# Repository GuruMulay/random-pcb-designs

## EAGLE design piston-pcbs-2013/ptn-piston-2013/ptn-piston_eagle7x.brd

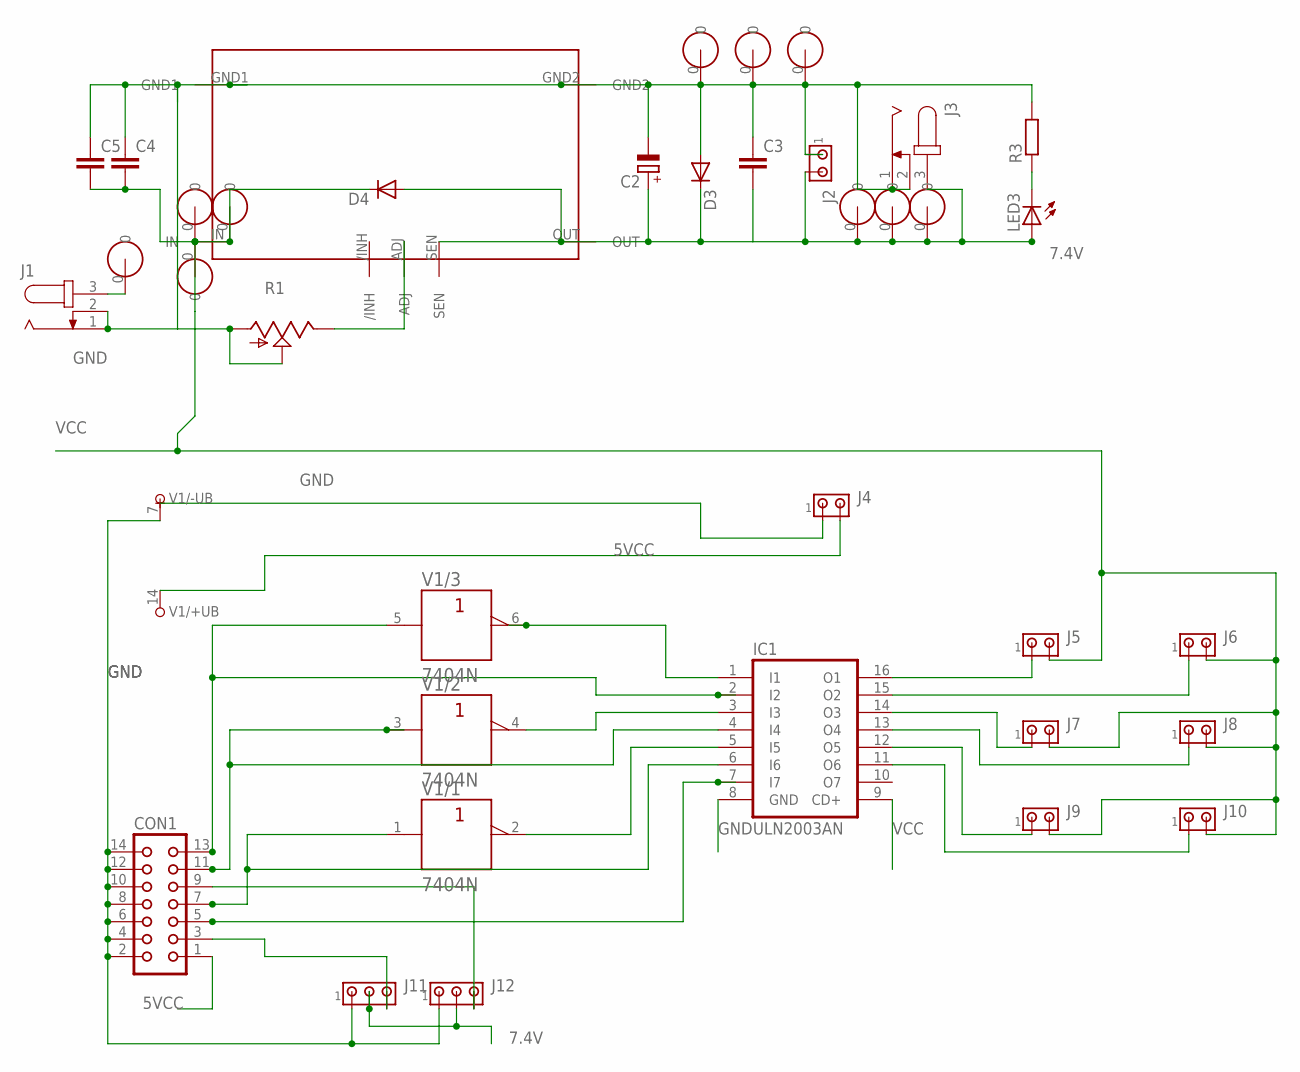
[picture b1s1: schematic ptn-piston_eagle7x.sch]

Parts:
C2: CPOL-EUE3.5-8; E3,5-8
C3, C4, C5: C-EUC1206K; C1206K
CON1: CON14
D3, D4: DIODE-SMB; SMB
IC1: ULN2003AN; DIL16
J1, J3: JACK-PLUG1; SPC4078
J2, J4, J5, J6, J7, J8, J9, J10: MTA02-100; 10X02MTA
J11, J12: MTA03-100; 10X03MTA
LED3: LED3MM
R1: TRIM_US-B64Y; B64Y
R3: R-EU_R0603; R0603
U$1: PTNPTN2; PTN
U$2: PAD0; SWITCHPAD
U$3, U$4, U$5, U$6, U$7, U$8, U$9, U$10, U$11: PADSWITCHPAD1; SWITCHPAD
V1: 7404N; DIL14

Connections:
5VCC: CON1.1, J4.2, V1.14 (+UB)
7.4V: C2.+, C3.2, D3.C, D4.A, J2.2, J3.3, J11.2, J12.2, LED3.A, U$1.OUT, U$1.SEN, U$5.0, U$7.0, U$9.0
GND: C2.-, C3.1, C4.1, C5.1, CON1.2, CON1.4, CON1.6, CON1.8, CON1.10, CON1.12, CON1.14, D3.A, IC1.8 (GND), J1.1, J1.2, J2.1, J3.1, J3.2, J4.1, J11.1, J12.1, R1.A, R1.S, R3.2, U$1.GND1, U$1.GND2, U$4.0, U$6.0, U$8.0, V1.7 (-UB)
unnamed: CON1.13, IC1.2 (I2), V1.5 (A)
unnamed: LED3.K (C), R3.1
unnamed: R1.E, U$1.ADJ
unnamed: CON1.11, IC1.4 (I4), V1.3 (A)
unnamed: J1.3, U$3.0
unnamed: CON1.7, IC1.6 (I6), V1.1 (A)
unnamed: IC1.5 (I5), V1.2 (Y)
unnamed: CON1.5, IC1.7 (I7)
unnamed: IC1.1 (I1), V1.6 (Y)
unnamed: IC1.3 (I3), V1.4 (Y)
unnamed: CON1.3, J11.3
unnamed: CON1.9, J12.3
unnamed: IC1.16 (O1), J5.1
unnamed: IC1.15 (O2), J6.1
unnamed: IC1.14 (O3), J7.1
unnamed: IC1.13 (O4), J8.1
unnamed: IC1.12 (O5), J9.1
unnamed: IC1.11 (O6), J10.1
VCC: C4.2, C5.2, D4.C, IC1.9 (CD+), J5.2, J6.2, J7.2, J8.2, J9.2, J10.2, U$1.IN, U$2.0, U$10.0, U$11.0

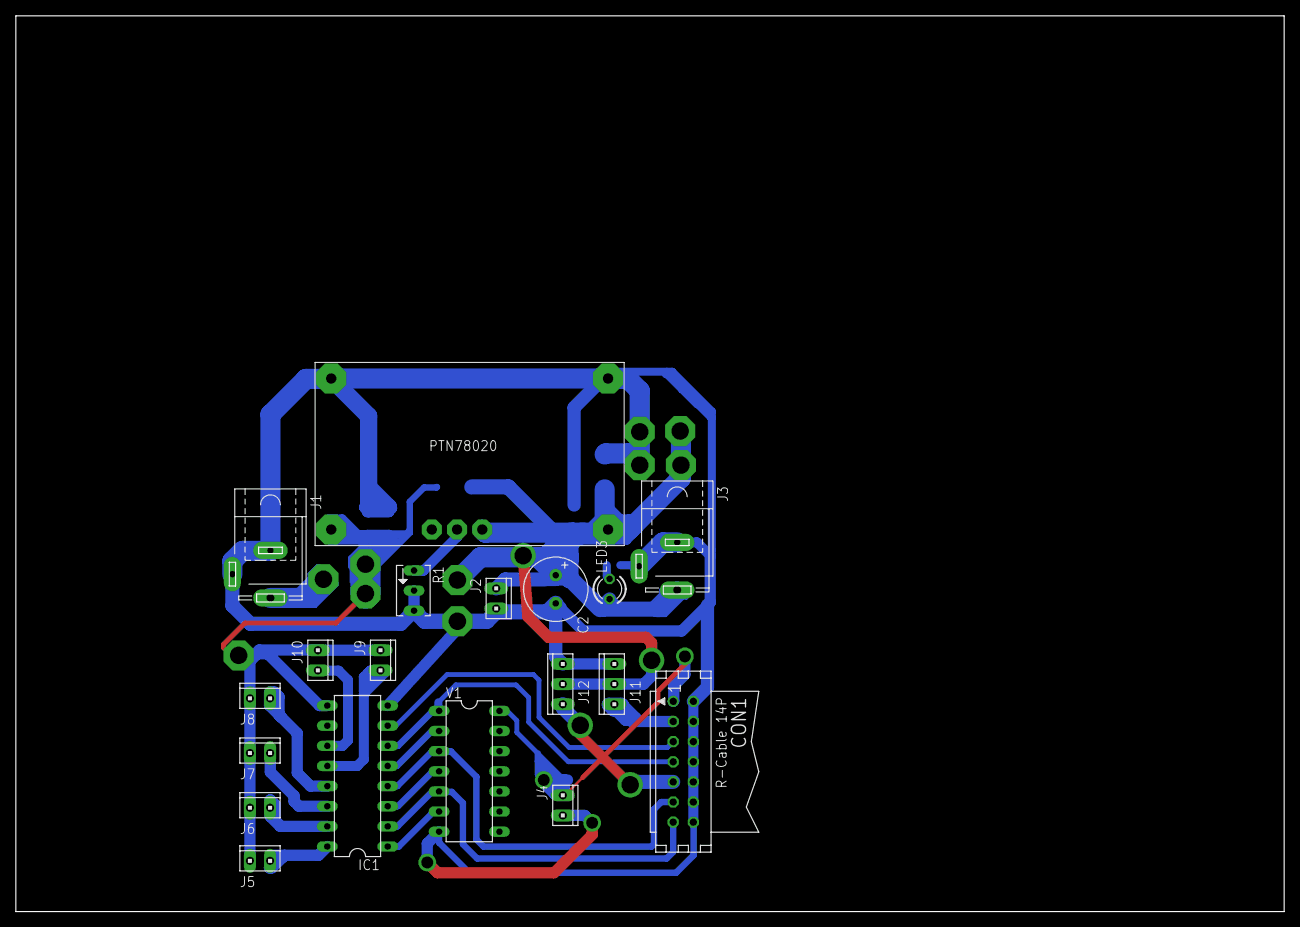
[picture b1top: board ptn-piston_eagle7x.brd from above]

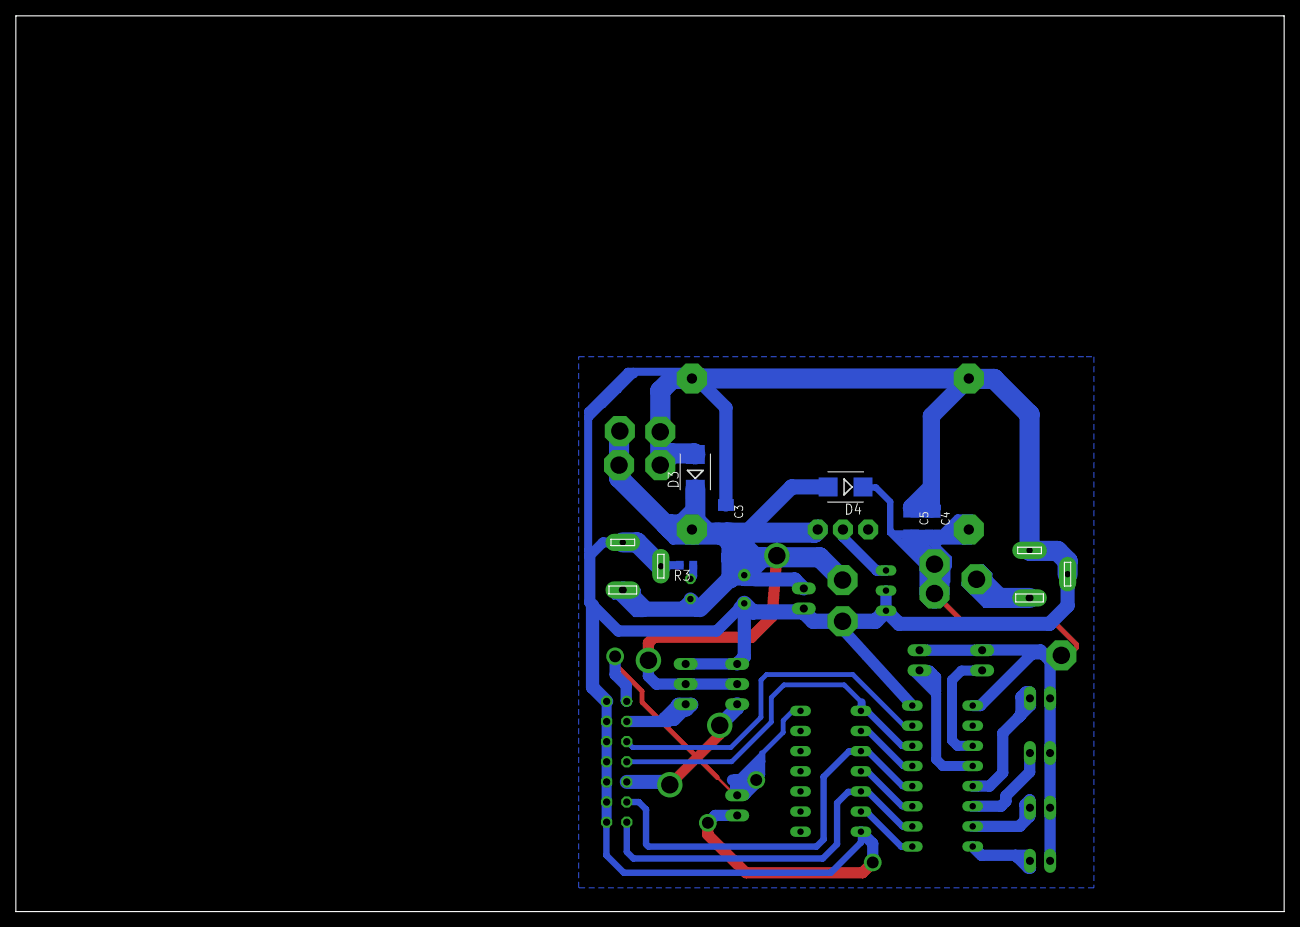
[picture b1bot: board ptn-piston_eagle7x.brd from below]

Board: 2 copper layers, 160.0 x 113.0 mm, 35 parts (6 on the bottom side), 22 nets.

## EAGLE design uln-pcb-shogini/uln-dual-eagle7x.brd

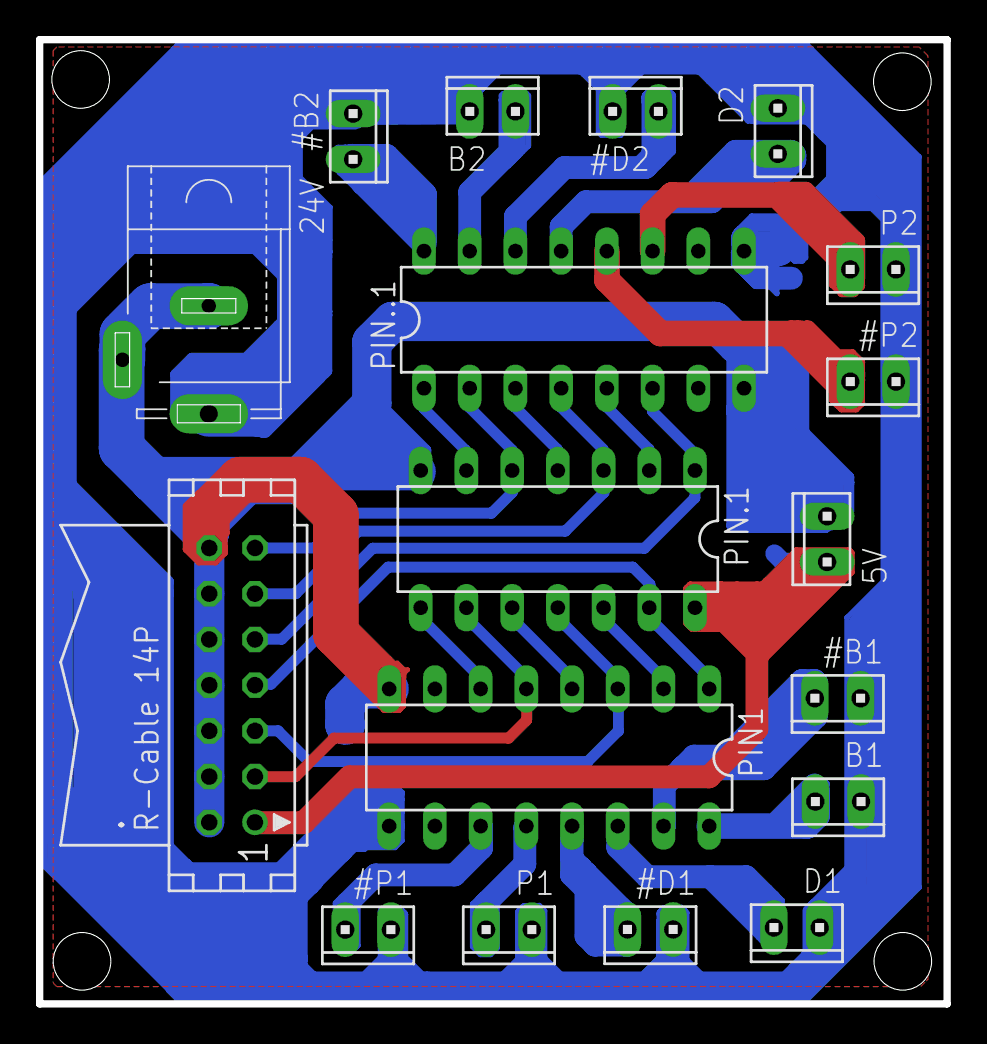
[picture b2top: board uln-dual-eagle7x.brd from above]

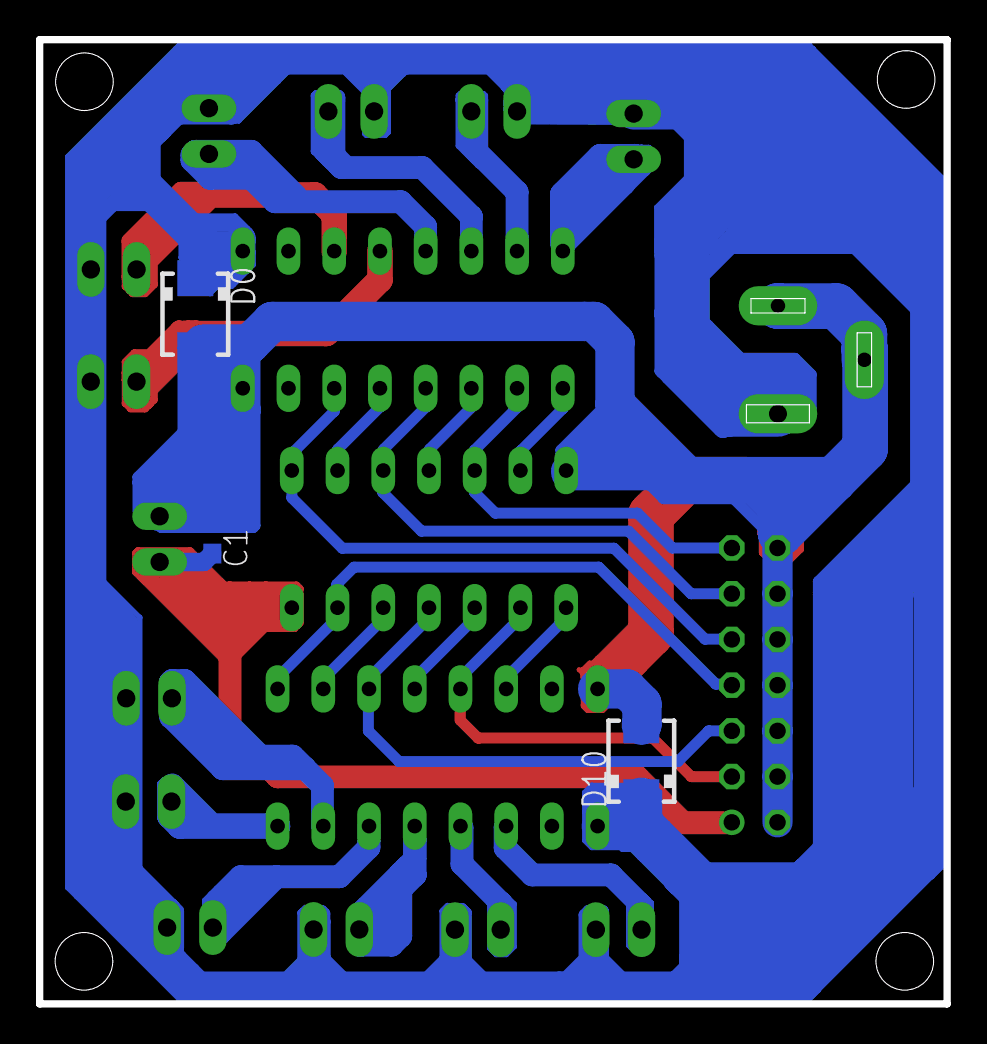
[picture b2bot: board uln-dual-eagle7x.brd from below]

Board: 2 copper layers, 50.4 x 53.6 mm, 21 parts (3 on the bottom side), 27 nets.

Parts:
5V: 10X02MTA
24V: SPC4078
#B1, #B2: 10X02MTA
#D1, #D2: 10X02MTA
#P1, #P2: 10X02MTA
.: CON14
B1, B2: 10X02MTA
C1: C0603
D0, D10: SMA
D1, D2: 10X02MTA
P1, P2: 10X02MTA
PIN1, PIN..1: ULN2003AN; DIL16
PIN.1: 7404N; DIL14

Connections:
5VCC: 5V.2, ..1, C1.2, PIN.1.14
GND: 5V.1, 24V.1, 24V.2, ..2, ..4, ..6, ..8, ..10, ..12, ..14, C1.1, D0.A, D10.A, PIN1.8, PIN.1.7, PIN..1.8
unnamed: PIN.1.4, PIN..1.3
unnamed: PIN.1.2, PIN..1.5
unnamed: ..13, PIN.1.5, PIN..1.2
unnamed: ..7, PIN1.1, PIN.1.13
unnamed: ..11, PIN.1.3, PIN..1.4
unnamed: PIN.1.6, PIN..1.1
unnamed: ..9, PIN.1.1, PIN..1.6
unnamed: ..5, PIN1.3, PIN.1.11
unnamed: ..3, PIN1.5, PIN.1.9
unnamed: PIN1.2, PIN.1.12
unnamed: PIN1.4, PIN.1.10
unnamed: PIN1.6, PIN.1.8
unnamed: #B2.1, PIN..1.16
unnamed: B2.1, PIN..1.15
unnamed: #D2.1, PIN..1.14
unnamed: D2.1, PIN..1.13
unnamed: #P2.1, PIN..1.12
unnamed: P2.1, PIN..1.11
unnamed: B1.1, PIN1.16
unnamed: D1.1, PIN1.14
unnamed: #D1.1, PIN1.13
unnamed: P1.1, PIN1.12
unnamed: #P1.1, PIN1.11
unnamed: #B1.1, PIN1.15
VCC: 24V.3, #B1.2, #B2.2, #D1.2, #D2.2, #P1.2, #P2.2, B1.2, B2.2, D0.C, D1.2, D2.2, D10.C, P1.2, P2.2, PIN1.9, PIN..1.9
